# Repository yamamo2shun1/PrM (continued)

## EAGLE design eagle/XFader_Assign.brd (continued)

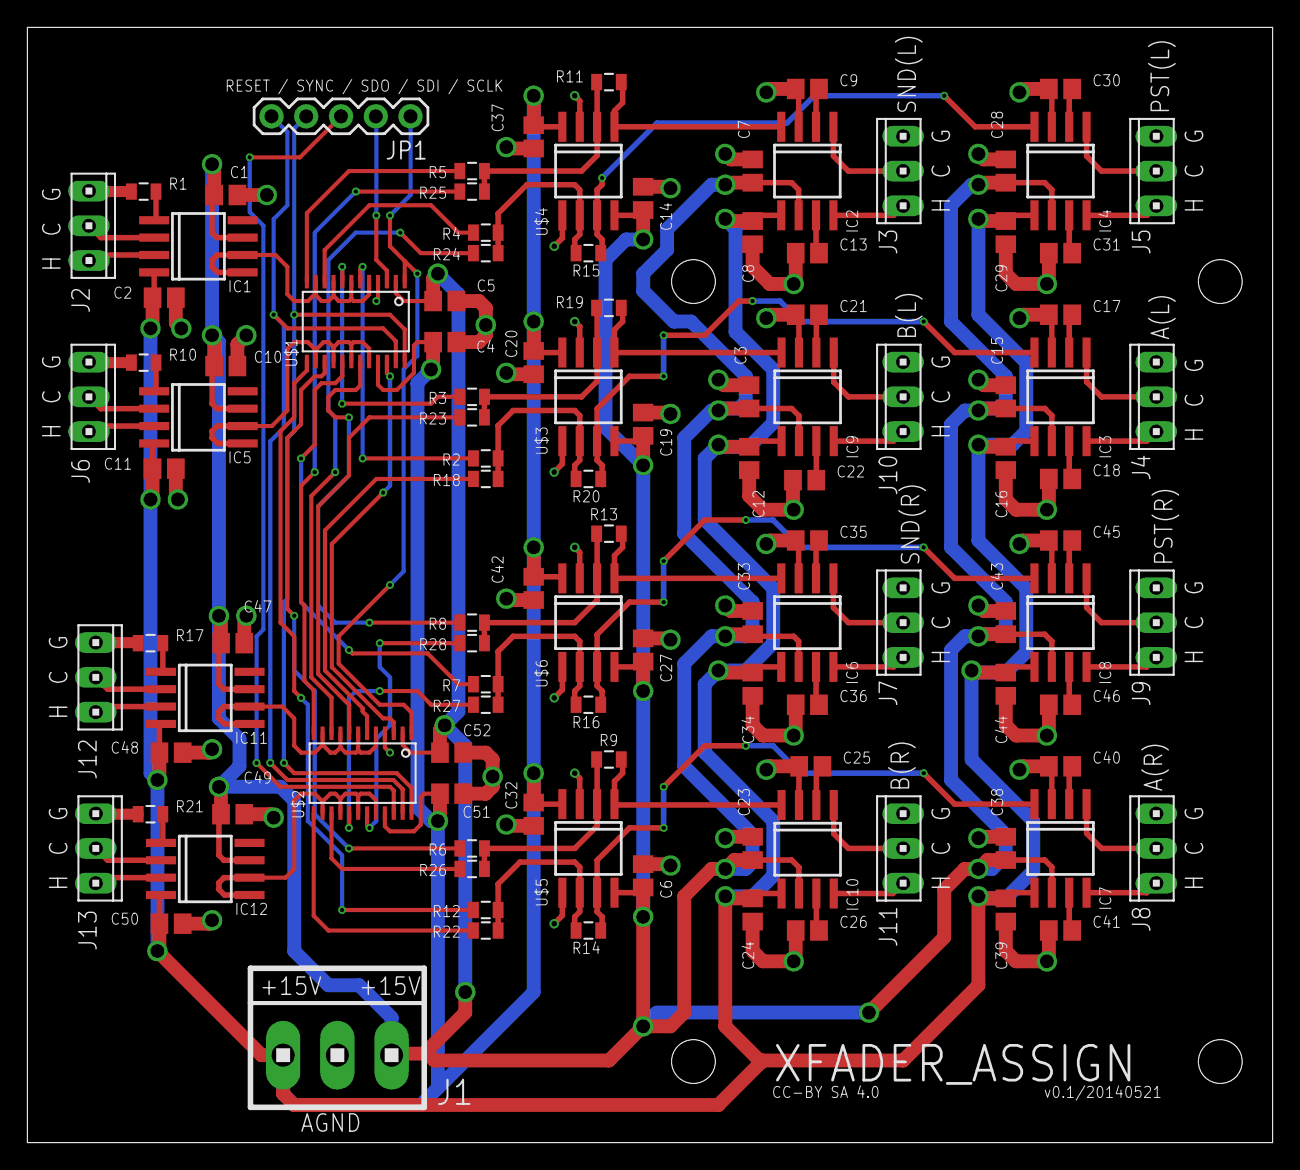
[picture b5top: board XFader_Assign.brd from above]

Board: 4 copper layers, 91.0 x 81.5 mm, 112 parts (0 on the bottom side), 89 nets.

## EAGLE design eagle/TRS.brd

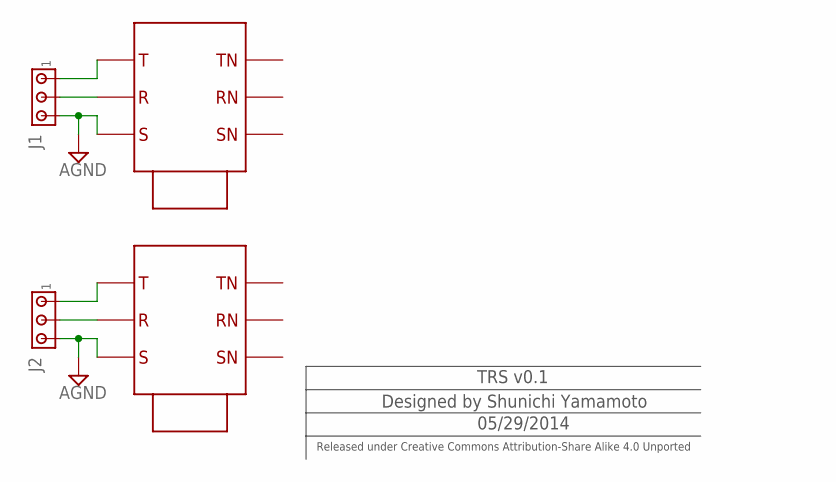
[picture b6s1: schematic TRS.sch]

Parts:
J1, J2: MTA03-100; 10X03MTA
X1, X2: NMJ6HFD2

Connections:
AGND: J1.3, J2.3, X1.GND-IN, X2.GND-IN
unnamed: J1.1, X1.LEFT-IN
unnamed: J1.2, X1.RIGHT-IN
unnamed: J2.1, X2.LEFT-IN
unnamed: J2.2, X2.RIGHT-IN

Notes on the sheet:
TRS v0.1
Designed by Shunichi Yamamoto
05/29/2014
Released under Creative Commons Attribution-Share Alike 4.0 Unported

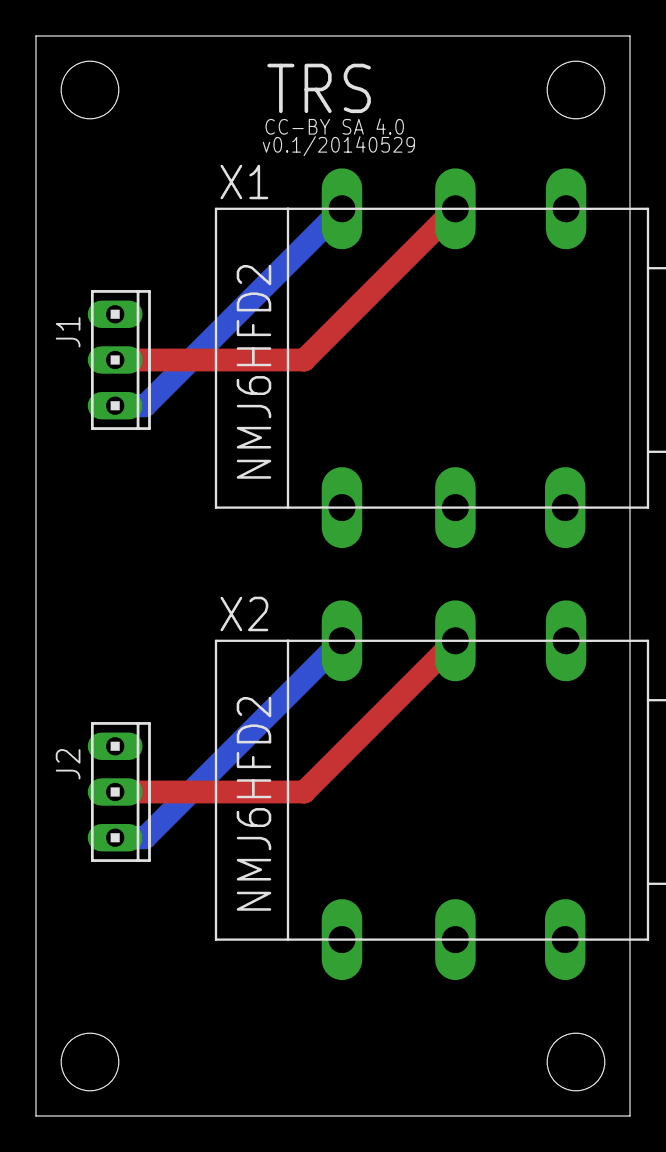
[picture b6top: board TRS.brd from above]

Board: 2 copper layers, 33.0 x 60.0 mm, 4 parts (0 on the bottom side), 5 nets.

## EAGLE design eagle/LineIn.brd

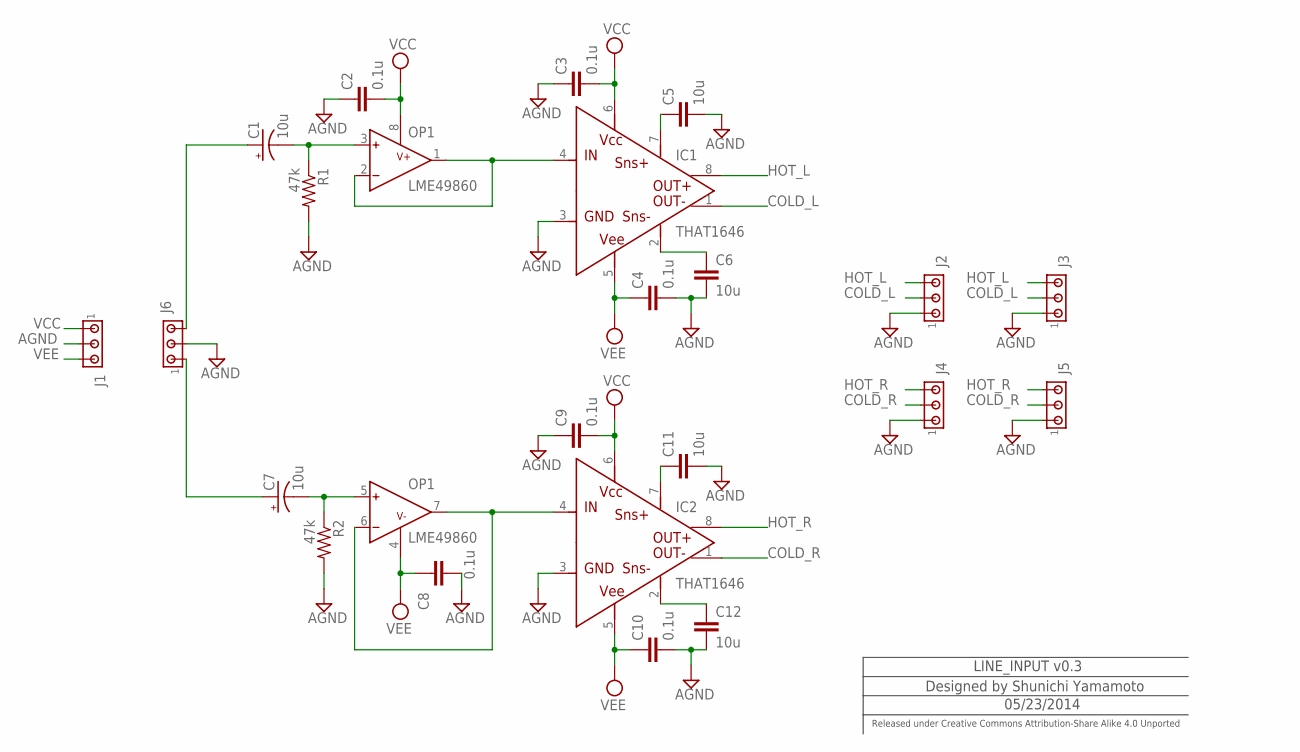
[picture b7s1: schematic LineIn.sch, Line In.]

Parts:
C1, C7: 10u; UD-5X5,8_NICHICON
C2, C3, C4, C8, C9, C10: 0.1u; C2012
C5, C6, C11, C12: 10u; C2012
IC1, IC2: THAT1646; SOIC8
J1: MTA03-156; 1X3MTA
J2, J3, J4, J5, J6: MTA03-100; 10X03MTA
OP1: LME49860; SOIC8@1
R1, R2: 47k; 0805

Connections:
AGND: C2.1, C3.1, C4.2, C5.2, C6.2, C8.2, C9.1, C10.2, C11.2, C12.2, IC1.3 (GND), IC2.3 (GND), J1.2, J2.1, J3.1, J4.1, J5.1, J6.2, R1.2, R2.2
COLD_L: IC1.1 (OUT-), J2.2, J3.2
COLD_R: IC2.1 (OUT-), J4.2, J5.2
HOT_L: IC1.8 (OUT+), J2.3, J3.3
HOT_R: IC2.8 (OUT+), J4.3, J5.3
LIN_L: IC1.4 (IN), OP1.1 (OUTA), OP1.2 (INA-)
LIN_R: IC2.4 (IN), OP1.6 (INB-), OP1.7 (OUTB)
unnamed: C1.+, J6.3
unnamed: C1.-, OP1.3 (INA+), R1.1
unnamed: C7.+, J6.1
unnamed: C5.1, IC1.7 (SNS+)
unnamed: C7.-, OP1.5 (INB+), R2.1
unnamed: C11.1, IC2.7 (SNS+)
unnamed: C6.1, IC1.2 (SNS-)
unnamed: C12.1, IC2.2 (SNS-)
VCC: C2.2, C3.2, C9.2, IC1.6 (VCC), IC2.6 (VCC), J1.1, OP1.8 (V+)
VEE: C4.1, C8.1, C10.1, IC1.5 (VEE), IC2.5 (VEE), J1.3, OP1.4 (V-)

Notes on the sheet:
LINE_INPUT v0.3
Designed by Shunichi Yamamoto
05/23/2014
Released under Creative Commons Attribution-Share Alike 4.0 Unported

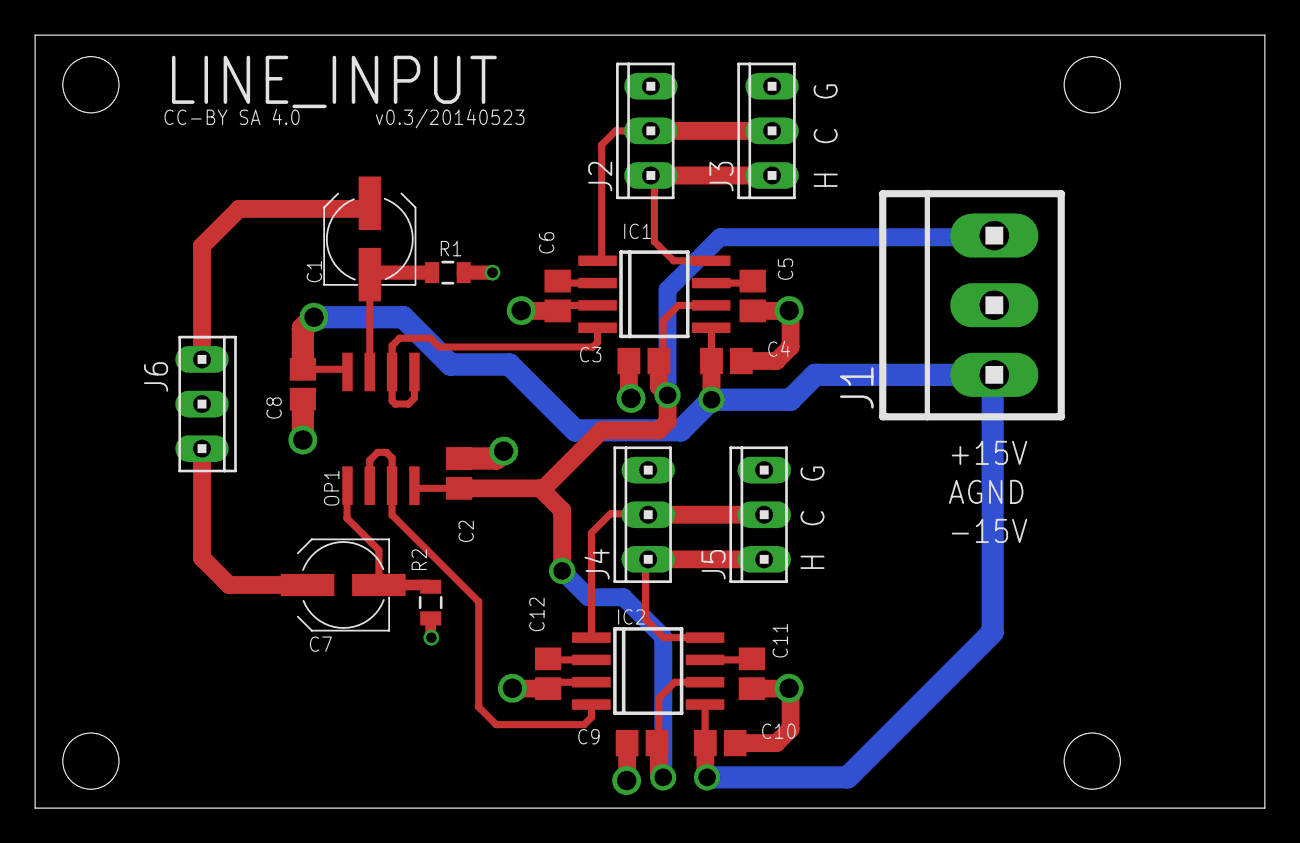
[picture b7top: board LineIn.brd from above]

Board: 2 copper layers, 70.0 x 44.0 mm, 23 parts (0 on the bottom side), 17 nets.

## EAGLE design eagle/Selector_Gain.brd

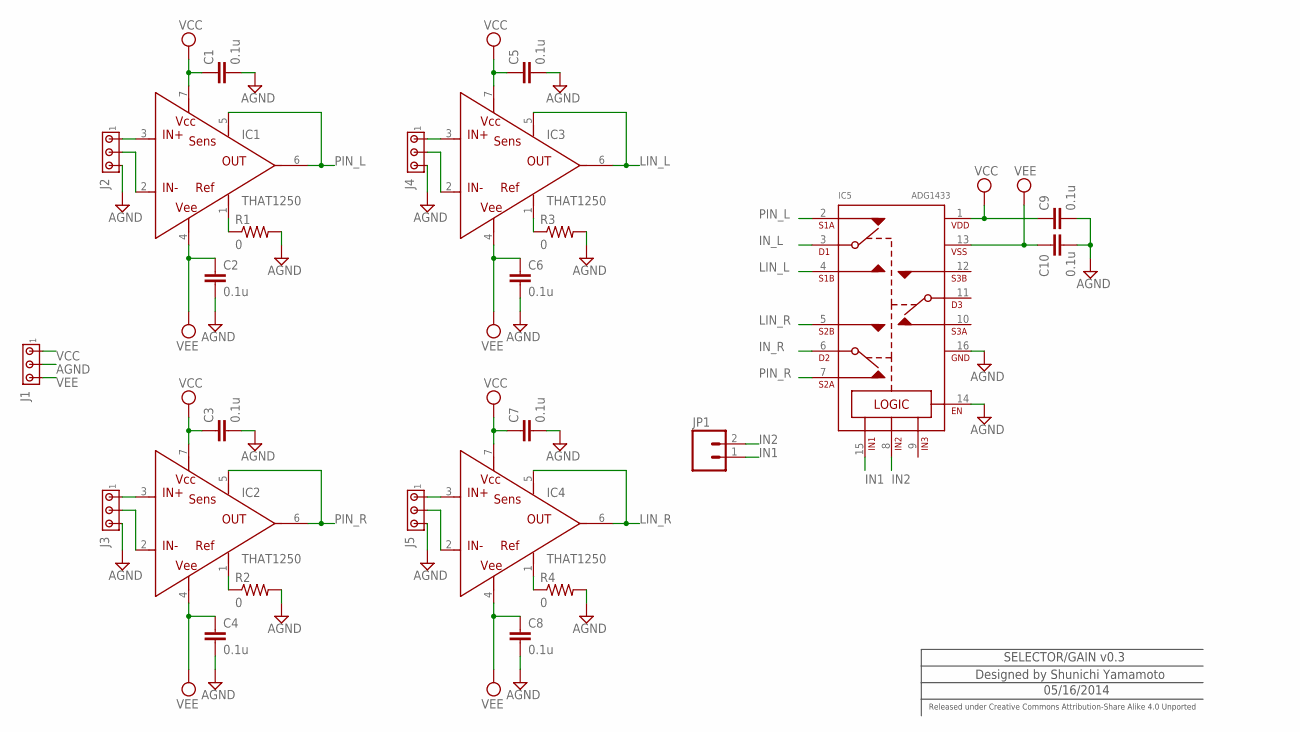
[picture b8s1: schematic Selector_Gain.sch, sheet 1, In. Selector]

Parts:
C1, C2, C3, C4, C5, C6, C7, C8, C9, C10: 0.1u; C2012
IC1, IC2, IC3, IC4: THAT1250; SOIC8
IC5: ADG1433; TSSOP16
J1: MTA03-156; 1X3MTA
J2, J3, J4, J5: MTA03-100; 10X03MTA
JP1: M02PTH; 1X02
R1, R2, R3, R4: 0; 0805

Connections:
AGND: C1.2, C2.2, C3.2, C4.2, C5.2, C6.2, C7.2, C8.2, C9.2, C10.2, IC5.14 (EN), IC5.16 (GND), J1.2, J2.3, J3.3, J4.3, J5.3, R1.2, R2.2, R3.2, R4.2; also elsewhere on the board
IN1: IC5.15 (IN1), JP1.1
IN2: IC5.8 (IN2), JP1.2
IN_L: IC5.3 (D1); also elsewhere on the board
IN_R: IC5.6 (D2); also elsewhere on the board
LIN_L: IC3.5 (SENS), IC3.6 (OUT), IC5.4 (S1B)
LIN_R: IC4.5 (SENS), IC4.6 (OUT), IC5.5 (S2B)
unnamed: IC1.1 (REF), R1.1
unnamed: IC3.1 (REF), R3.1
unnamed: IC1.3 (IN+), J2.1
unnamed: IC1.2 (IN-), J2.2
unnamed: IC2.1 (REF), R2.1
unnamed: IC3.3 (IN+), J4.1
unnamed: IC2.3 (IN+), J3.1
unnamed: IC2.2 (IN-), J3.2
unnamed: IC3.2 (IN-), J4.2
unnamed: IC4.1 (REF), R4.1
unnamed: IC4.3 (IN+), J5.1
unnamed: IC4.2 (IN-), J5.2
PIN_L: IC1.5 (SENS), IC1.6 (OUT), IC5.2 (S1A)
PIN_R: IC2.5 (SENS), IC2.6 (OUT), IC5.7 (S2A)
VCC: C1.1, C3.1, C5.1, C7.1, C9.1, IC1.7 (VCC), IC2.7 (VCC), IC3.7 (VCC), IC4.7 (VCC), IC5.1 (VDD), J1.1; also elsewhere on the board
VEE: C2.1, C4.1, C6.1, C8.1, C10.1, IC1.4 (VEE), IC2.4 (VEE), IC3.4 (VEE), IC4.4 (VEE), IC5.13 (VSS), J1.3; also elsewhere on the board

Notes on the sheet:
SELECTOR/GAIN v0.3
Designed by Shunichi Yamamoto
05/16/2014
Released under Creative Commons Attribution-Share Alike 4.0 Unported

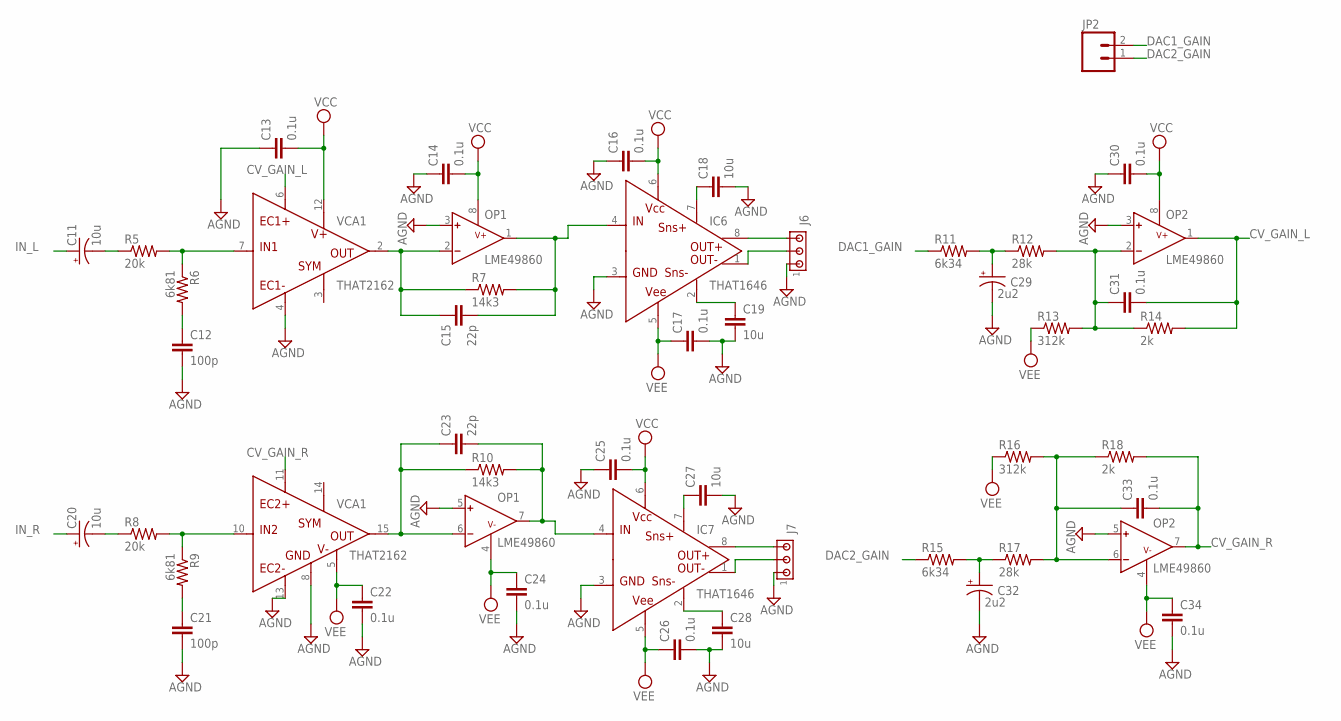
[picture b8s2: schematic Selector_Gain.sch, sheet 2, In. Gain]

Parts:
C11, C20: 10u; UD-5X5,8_NICHICON
C12, C21: 100p; C2012
C13, C14, C16, C17, C22, C24, C25, C26, C30, C31, C33, C34: 0.1u; C2012
C15, C23: 22p; C2012
C18, C19, C27, C28: 10u; C2012
C29, C32: 2u2; UD-5X5,8_NICHICON
IC6, IC7: THAT1646; SOIC8
J6, J7: MTA03-100; 10X03MTA
JP2: M02PTH; 1X02
OP1, OP2: LME49860; SOIC8
R5, R8: 20k; 0805
R6, R9: 6k81; 0805
R7, R10: 14k3; 0805
R11, R15: 6k34; 0805
R12, R17: 28k; 0805
R13, R16: 312k; 0805
R14, R18: 2k; 0805
VCA1: THAT2162; QSOP-16

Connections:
AGND: C12.2, C13.1, C14.1, C16.1, C17.2, C18.2, C19.2, C21.2, C22.2, C24.2, C25.1, C26.2, C27.2, C28.2, C29.-, C30.1, C32.-, C34.2, IC6.3 (GND), IC7.3 (GND), J6.1, J7.1, OP1.3 (INA+), OP1.5 (INB+), OP2.3 (INA+), OP2.5 (INB+), VCA1.4 (EC1-), VCA1.8 (GND), VCA1.13 (EC2-); also elsewhere on the board
CV_GAIN_L: C31.2, OP2.1 (OUTA), R14.2, VCA1.6 (EC1+)
CV_GAIN_R: C33.2, OP2.7 (OUTB), R18.2, VCA1.11 (EC2+)
DAC1_GAIN: JP2.2, R11.1
DAC2_GAIN: JP2.1, R15.1
IN_L: C11.+; also elsewhere on the board
IN_R: C20.+; also elsewhere on the board
unnamed: IC6.8 (OUT+), J6.3
unnamed: IC6.1 (OUT-), J6.2
unnamed: IC7.8 (OUT+), J7.3
unnamed: IC7.1 (OUT-), J7.2
unnamed: R5.2, R6.1, VCA1.7 (IN1)
unnamed: C11.-, R5.1
unnamed: C18.1, IC6.7 (SNS+)
unnamed: C19.1, IC6.2 (SNS-)
unnamed: C27.1, IC7.7 (SNS+)
unnamed: C28.1, IC7.2 (SNS-)
unnamed: R8.2, R9.1, VCA1.10 (IN2)
unnamed: C20.-, R8.1
unnamed: C12.1, R6.2
unnamed: C15.1, OP1.2 (INA-), R7.1, VCA1.2 (OUT1)
unnamed: C21.1, R9.2
unnamed: C29.+, R11.2, R12.1
unnamed: C31.1, OP2.2 (INA-), R12.2, R13.2, R14.1
unnamed: C32.+, R15.2, R17.1
unnamed: C33.1, OP2.6 (INB-), R16.2, R17.2, R18.1
unnamed: C23.1, OP1.6 (INB-), R10.1, VCA1.15 (OUT2)
OUT_L: C15.2, IC6.4 (IN), OP1.1 (OUTA), R7.2
OUT_R: C23.2, IC7.4 (IN), OP1.7 (OUTB), R10.2
VCC: C13.2, C14.2, C16.2, C25.2, C30.2, IC6.6 (VCC), IC7.6 (VCC), OP1.8 (V+), OP2.8 (V+), VCA1.12 (V+); also elsewhere on the board
VEE: C17.1, C22.1, C24.1, C26.1, C34.1, IC6.5 (VEE), IC7.5 (VEE), OP1.4 (V-), OP2.4 (V-), R13.1, R16.1, VCA1.5 (V-); also elsewhere on the board

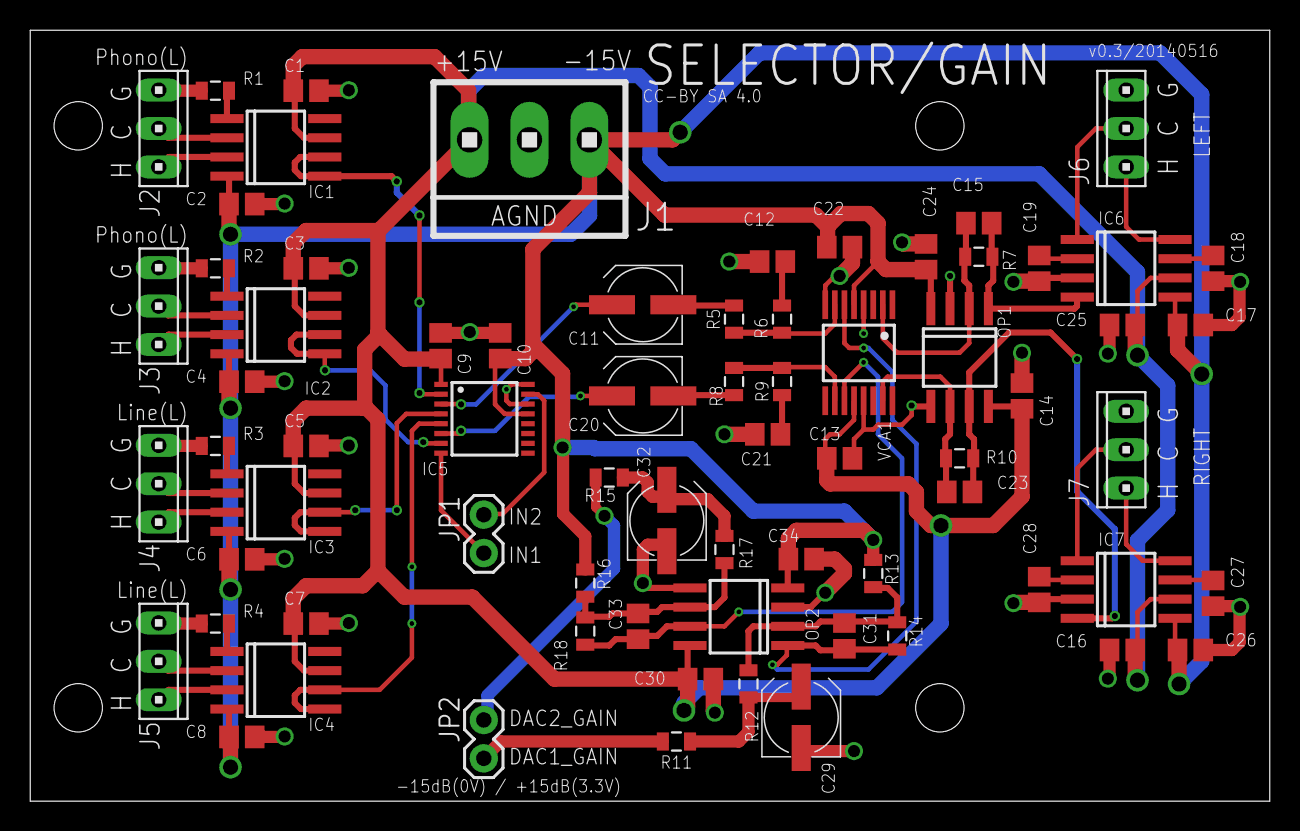
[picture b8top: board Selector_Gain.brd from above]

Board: 2 copper layers, 82.0 x 51.0 mm, 71 parts (0 on the bottom side), 49 nets.

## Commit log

2014-05-29 Add schematic and board datas.
2014-05-30 Add the basic connection diagram.
2014-05-30 Added the eagle files(.sch and .brd).
2014-05-30 Update README.
